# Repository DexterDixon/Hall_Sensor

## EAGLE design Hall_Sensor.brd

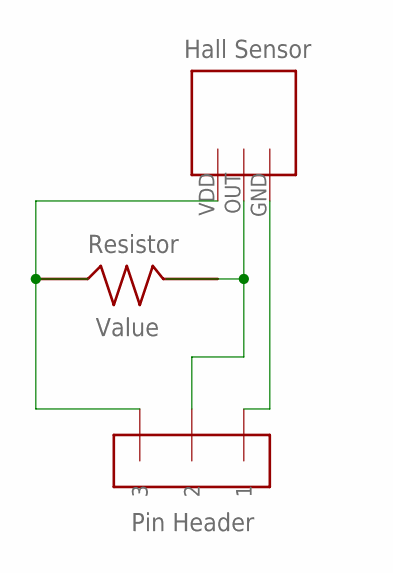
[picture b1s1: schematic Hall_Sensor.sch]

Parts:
U$9: HALL_SENSOR
U$10: PIN_HEADER
U$11: RESISTOR

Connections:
unnamed: U$9.OUT, U$10.2, U$11.2
unnamed: U$9.VDD, U$10.3, U$11.1
unnamed: U$9.GND, U$10.1

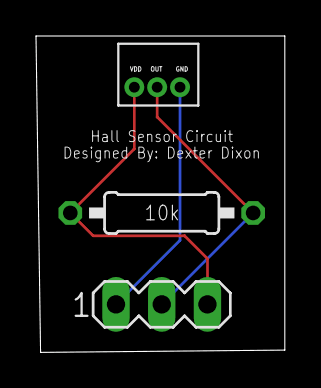
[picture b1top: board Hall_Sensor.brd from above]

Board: 2 copper layers, 13.8 x 17.6 mm, 3 parts (0 on the bottom side), 3 nets.
